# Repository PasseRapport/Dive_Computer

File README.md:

# Freediving Computer

A wrist-mounted freediving computer with tap navigation, wireless charging, and a fully sealed enclosure — no buttons, no external connectors.

---

## V1 — Proof of Concept

Proved two core ideas: **tap-based navigation** via accelerometer and **wireless charging** inside a completely sealed case.

| | |
|---|---|
| **MCU** | ESP32-C3 |
| **Display** | 1.27″ SSD1351 color OLED (128×96) |
| **Pressure** | MS5837-30BA — ±2 mm resolution |
| **Navigation** | LIS2DUX12 tap detection — no buttons |
| **Charging** | LTC4120 wireless receiver — no connectors |
| **Switch** | Magnetic battery cutoff — true 0 µA storage |

### Interface

<p align="center"><em>Tap-based menu navigation — accelerometer detects directional impacts on the casing.</em></p>

### In the Water

<p align="center"><em>Live depth tracking — automatic dive detection and surface recovery timer.</em></p>

### Enclosure

Two-part sandwich assembly sealed by a perimeter O-ring and 12 M2 screws. No dynamic seals anywhere.

---

## V2 — Work in Progress

More compact, better component integration, and additional sensors.

### PCB

### 3D Model

### Exploded View

---

## Android Companion

The offline Android app, Linux BLE watch simulator, and protocol tests live in [`app/`](app/README.md). Development is on a dedicated branch; V1 and V2 firmware remain independent.

## Repository Structure

```
Dive_Computer/
├── V1/         # Prototype — full firmware + hardware source files
├── V2/         # Current revision — in progress
└── app/        # Android companion, BLE simulator and protocol tests
```

See [`V1/README.md`](V1/README.md) for detailed hardware architecture, firmware design, and dive state machine documentation.

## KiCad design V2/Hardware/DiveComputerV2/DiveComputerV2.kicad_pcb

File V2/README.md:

# Freediving Computer V2

## 3D

## Exploded View

## PCB

## Schematic

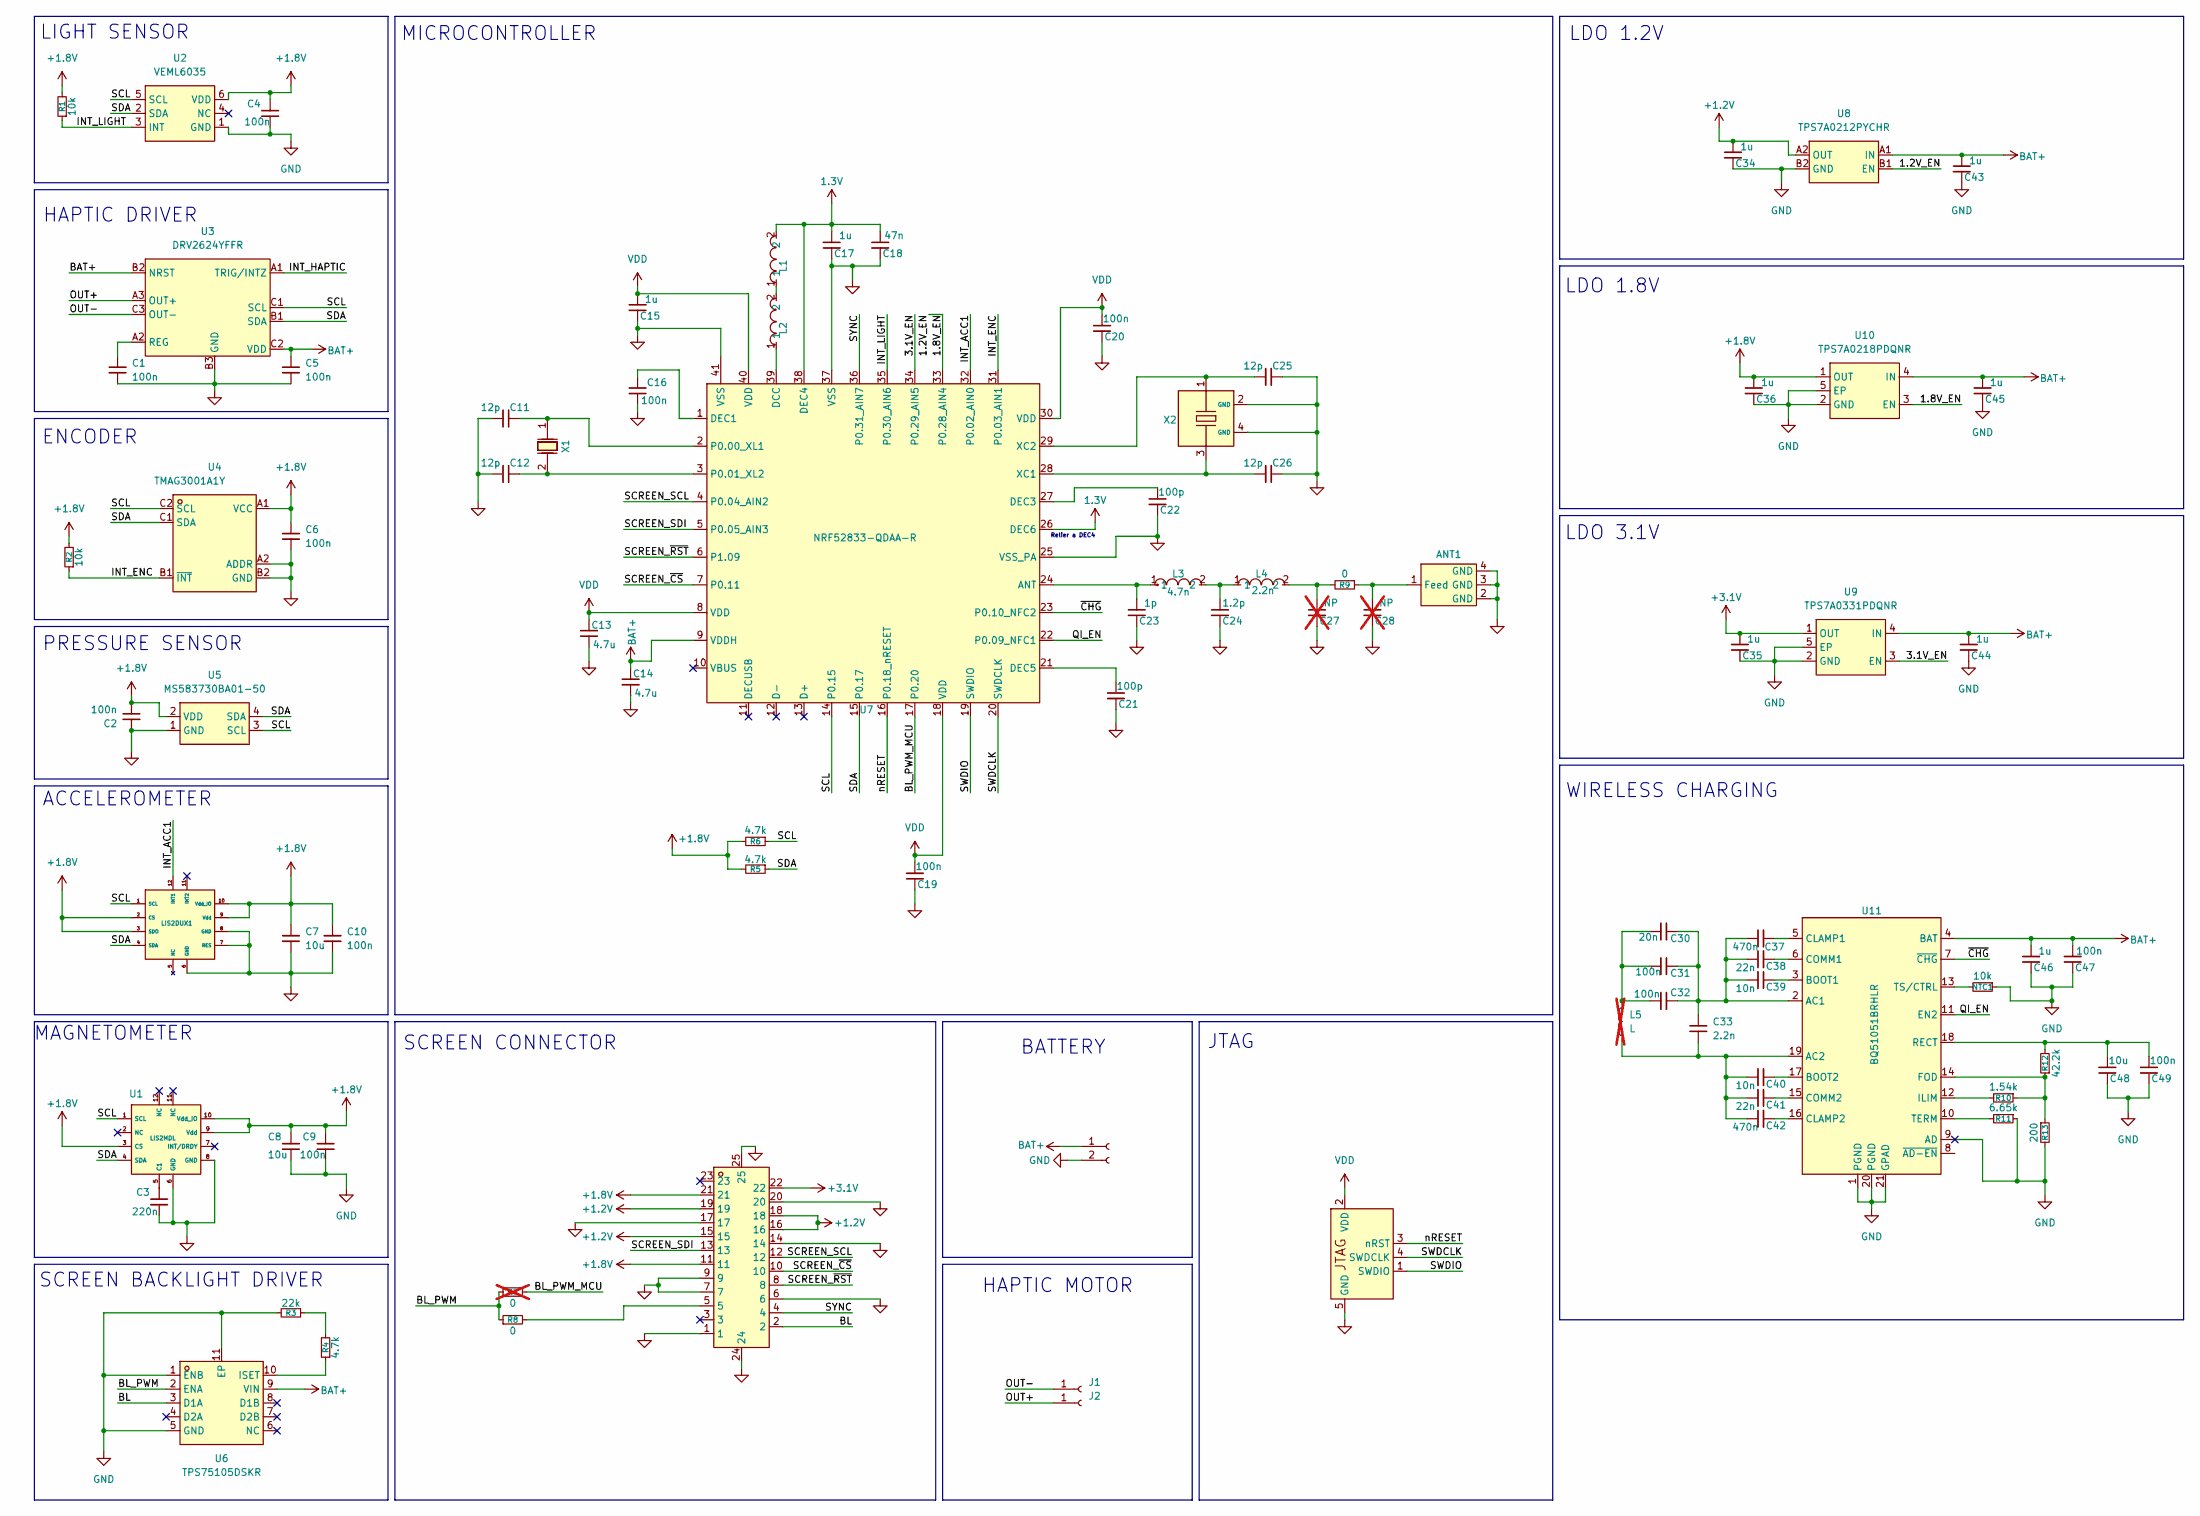
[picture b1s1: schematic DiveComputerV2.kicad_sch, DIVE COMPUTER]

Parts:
ANT1: 2450AT18D0100E; ANT-SMD_4P-L3.2-W1.6; MPN 2450AT18D0100E; LCSC Part C2917718
C1, C2, C4, C5, C6, C9, C10, C47: 100n; C_0402_1005Metric; MPN CL05B104KO5NNNC; LCSC Part C1525
C3: 220n; C_0402_1005Metric; MPN CL05B224KO5NNNC; LCSC Part C16772
C7, C8: 10u; C_0402_1005Metric; LCSC Part C15525
C11, C12, C25, C26: 12p; C_0402_1005Metric; MPN 0402CG120J500NT; LCSC Part C1547
C13, C14: 4.7u; C_0402_1005Metric; LCSC Part C23733
C15, C34, C35, C36, C43, C44, C45, C46: 1u; C_0402_1005Metric; MPN CL05A105KA5NQNC; LCSC Part C52923
C16, C19, C20, C49: 100n; C_0402_1005Metric; MPN CL05B104KB54PNC; LCSC Part C307331
C17: 1u; C_0402_1005Metric; MPN TCC0402X7R105K250AT; LCSC Part C53426846
C18: 47n; C_0402_1005Metric; MPN CL05B473KO5NNNC; LCSC Part C307434
C21, C22: 100p; C_0402_1005Metric; MPN 0402CG101J500NT; LCSC Part C1546
C23: 1p; C_0402_1005Metric; MPN GJM1555C1H1R0WB01D; LCSC Part C72134
C24: 1.2p; C_0402_1005Metric; MPN GJM1555C1H1R2WB01D; LCSC Part C76899
C27, C28: NP; C_0402_1005Metric; not fitted
C29: SAH_Connect
C30: 20n; C_0805_2012Metric; Voltage 50V; Tolerance 1%; MPN GCM21B5C1H203FA16L; LCSC Part C17588990
C31, C32: 100n; C_1206_3216Metric; Voltage 50V; Tolerance 5%; MPN GRM31C5C1H104JA01L; LCSC Part C97946
C33: 2.2n; C_0402_1005Metric; MPN GRM1555C1H222GA01D; LCSC Part C2987940
C37, C42: 470n; C_0402_1005Metric; MPN GRM155R61E474KE01D; LCSC Part C437526
C38, C41: 22n; C_0402_1005Metric; MPN 0402B223K500NT; LCSC Part C1532
C39, C40: 10n; C_0402_1005Metric; MPN GRM155R71H103KA88J; LCSC Part C2840480
C48: 10u; C_0603_1608Metric; MPN CL10A106MA8NRNC; LCSC Part C96446
FPC1: FH35C-23S-0.3SHW; FPC-SMD_23P-P0.60_HRS_FH35C-23S-0.3SHW; MPN FH35C-23S-0.3SHW(50); LCSC Part C2889270
J1, J2: Conn_01x01_Socket; 2292838-3
J3: Conn_01x02_Socket; THT Solder PAD 2pin
L1: LQW15AN15NG00D; IND-SMD_L1.0-W0.5-2; MPN LQW15AN15NG00D; LCSC Part C98055
L2: LQM18DN100M70L; L0603; MPN LQM18DN100M70L; LCSC Part C713281
L3: 4.7n; L0402-RD; MPN LQG15HS4N7B02D; LCSC Part C162543
L4: 2.2n; L0402; MPN LQG15HS2N2B02D; LCSC Part C162540
L5: L; THT Solder PAD 2pin; not fitted
LIS2DUX1: LGA-12_2x2mm_P0.5mm; LCSC Part C17548754
NTC1: 10k; R_0402_1005Metric; MPN NCP15XH103F03RC; LCSC Part C77131
R1, R2: 10k; R_0402_1005Metric; MPN 0402WGF1002TCE; LCSC Part C25744
R3: 22k; R_0402_1005Metric; MPN 0402WGF2202TCE; LCSC Part C25768
R4, R5, R6: 4.7k; R_0402_1005Metric; MPN 0402WGF4701TCE; LCSC Part C25900
R7: 0; R_0402_1005Metric; LCSC Part C17168; not fitted
R8, R9: 0; R_0402_1005Metric; LCSC Part C17168
R10: 1.54k; R_0402_1005Metric; MPN CRCW04021K54FKED; LCSC Part C2085404
R11: 6.65k; R_0402_1005Metric; MPN CRCW04026K65FKED; LCSC Part C2076542
R12: 42.2k; R_0402_1005Metric; MPN FRC0402F4222TS; LCSC Part C5126131
R13: 200; R_0402_1005Metric; MPN 0402WGF2000TCE; LCSC Part C25087
U1: LIS2MDL; VLGA-12_L2.0-W2.0-P0.50-BL; MPN LIS2MDLTR; LCSC Part C919695
U2: VEML6035; SMD-6_L2.0-W2.0-P0.65-BL; MPN VEML6035; LCSC Part C2655158
U3: DRV2624YFFR; DSBGA-9_L1.4-W1.3-R3-C3-P0.40-BL; MPN DRV2624YFFR; LCSC Part C881487
U4: TMAG3001A1Y; BGA-6_L1.3-W0.8-P0.40-TL_PTMAG3001A2YBGR; MPN TMAG3001A1YBGR; LCSC Part C29073186
U5: MS583730BA01-50; SENSOR-SMD_4P-L3.3-W3.3-P2.00-BL; MPN MS583730BA01-50; LCSC Part C2887941
U6: TPS75105DSKR; WSON-10_L2.5-W2.5-W0.50-TL-EP; MPN TPS75105DSKR; LCSC Part C2859928
U7: NRF52833-QDAA-R; QFN-40_L5.0-W5.0-P0.40-TL-EP3.6; MPN nRF52833-QDAA-R; LCSC Part C2895249
U8: TPS7A0212PYCHR; DSBGA-4_L0.7-W0.7-R2-C2-P0.35-BL; MPN TPS7A0212PYCHR; LCSC Part C2918962
U9: TPS7A0331PDQNR; X2SON-4_L1.0-W1.0-P0.65-TL-EP; MPN TPS7A0331PDQNR; LCSC Part C2864441
U10: TPS7A0218PDQNR; X2SON-4_L1.0-W1.0-P0.65-TL-EP; MPN TPS7A0218PDQNR; LCSC Part C2862166
U11: BQ51051BRHLR; VQFN-20_L4.5-W3.5-P0.50-BL-EP_BQ24100RHLR; MPN BQ51051BRHLR; LCSC Part C2876732
X1: CM8V-T1A-32.768KHZ-9PF-20PPM-TB-QC; CRYSTAL-SMD_L2.0-W1.2; MPN CM8V-T1A-32.768kHz-9pF-20PPM-TB-QC; LCSC Part C5280691
X2: ECS-320-CDX-2152; CRYSTAL-SMD_4P-L1.6-W1.2-BL; MPN ECS-320-CDX-2152; LCSC Part C5686354

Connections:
1.3V: C17.2, C18.2, L1.2, U7.26 (DEC6), U7.38 (DEC4)
+1.2V: C34.2, FPC1.15, FPC1.16, FPC1.18, FPC1.19, U8.A2 (OUT)
+1.8V: C2.2, C4.1, C6.2, C7.1, C8.1, C9.1, C10.1, C36.2, FPC1.11, FPC1.21, LIS2DUX1.2 (CS), LIS2DUX1.3 (SDO), LIS2DUX1.9 (Vdd), LIS2DUX1.10 (Vdd_IO), R1.2, R2.2, R5.2, R6.2, U1.3 (CS), U1.9 (Vdd), U1.10 (Vdd_IO), U2.6 (VDD), U4.A1 (VCC), U5.2 (VDD), U10.1 (OUT)
+3.1V: C35.2, FPC1.22, U9.1 (OUT)
/1.2V_EN: U7.33 (P0.28_AIN4), U8.B1 (EN), U10.3 (EN)
/3.1V_EN: U7.34 (P0.29_AIN5), U9.3 (EN)
/BL: FPC1.2, U6.3 (D1A)
/BL_PWM: R7.1, R8.1, U6.2 (ENA)
/BL_PWM_MCU: R7.2, U7.17 (P0.20)
/INT_ACC1: LIS2DUX1.12 (INT1), U7.32 (P0.02_AIN0)
/INT_ENC: R2.1, U4.B1 (~INT), U7.31 (P0.03_AIN1)
/INT_HAPTIC: U3.A1 (TRIG/INTZ)
/INT_LIGHT: R1.1, U2.3 (INT), U7.35 (P0.30_AIN6)
/OUT+: J2.1 (Pin_1_1), U3.A3 (OUT+)
/OUT-: J1.1 (Pin_1_1), U3.C3 (OUT-)
/QI_EN: U7.22 (P0.09_NFC1), U11.11 (EN2)
/SCL: LIS2DUX1.1 (SCL), R6.1, U1.1 (SCL), U2.5 (SCL), U3.C1 (SCL), U4.C2 (SCL), U5.3 (SCL), U7.14 (P0.15)
/SCREEN_SCL: FPC1.12, U7.4 (P0.04_AIN2)
/SCREEN_SDI: FPC1.13, U7.5 (P0.05_AIN3)
/SCREEN_~CS: FPC1.10, U7.7 (P0.11)
/SCREEN_~RST: FPC1.8, U7.6 (P1.09)
/SDA: LIS2DUX1.4 (SDA), R5.1, U1.4 (SDA), U2.2 (SDA), U3.B1 (SDA), U4.C1 (SDA), U5.4 (SDA), U7.15 (P0.17)
/SWDCLK: C29.4 (SWDCLK), U7.20 (SWDCLK)
/SWDIO: C29.1 (SWDIO), U7.19 (SWDIO)
/SYNC: FPC1.4, U7.36 (P0.31_AIN7)
/nRESET: C29.3 (nRST), U7.16 (P0.18_nRESET)
/~CHG: U7.23 (P0.10_NFC2), U11.7 (~CHG)
BAT+: C5.1, C14.1, C43.2, C44.2, C45.2, C46.2, C47.2, J3.1, U3.B2 (NRST), U3.C2 (VDD), U6.9 (VIN), U7.9 (VDDH), U8.A1 (IN), U9.4 (IN), U10.4 (IN), U11.4 (BAT)
GND: ANT1.2 (GND), ANT1.3 (GND), ANT1.4 (GND), C1.2, C2.1, C3.2, C4.2, C5.2, C6.1, C7.2, C8.2, C9.2, C10.2, C11.2, C12.2, C13.2, C14.2, C15.1, C16.2, C17.1, C18.1, C19.1, C20.1, C21.1, C22.1, C23.1, C24.1, C25.1, C26.1, C27.1, C28.1, C29.5 (GND), C34.1, C35.1, C36.1, C43.1, C44.1, C45.1, C46.1, C47.1, C48.1, C49.1, FPC1.1, FPC1.6, FPC1.7, FPC1.9, FPC1.14, FPC1.17, FPC1.20, FPC1.24, FPC1.25, J3.2, LIS2DUX1.6 (GND), LIS2DUX1.7 (RES), LIS2DUX1.8 (GND), NTC1.1, R3.2, R11.1, R13.2, U1.6 (GND), U1.8 (GND), U2.1 (GND), U3.B3 (GND), U4.A2 (ADDR), U4.B2 (GND), U5.1 (GND), U6.1 (ENB), U6.5 (GND), U6.11 (EP), U7.25 (VSS_PA), U7.37 (VSS), U7.41 (VSS), U8.B2 (GND), U9.2 (GND), U9.5 (EP), U10.2 (GND), U10.5 (EP), U11.1 (PGND), U11.9 (AD), U11.20 (PGND), U11.21 (GPAD), X2.2 (GND), X2.4 (GND)
unnamed: ANT1.1 (Feed), C28.2, R9.1
unnamed: C24.2, L3.2, L4.1
unnamed: C27.2, L4.2, R9.2
unnamed: C30.1, C31.1, C32.1, L5.2
unnamed: FPC1.5, R8.2
unnamed: L1.1, L2.2
unnamed: R3.1, R4.2
unnamed: C3.1, U1.5 (C1)
unnamed: C1.1, U3.A2 (REG)
unnamed: R4.1, U6.10 (ISET)
unnamed: C23.2, L3.1, U7.24 (ANT)
unnamed: L2.1, U7.39 (DCC)
unnamed: C16.1, U7.1 (DEC1)
unnamed: C22.2, U7.27 (DEC3)
unnamed: C21.2, U7.21 (DEC5)
unnamed: C11.1, U7.2 (P0.00_XL1), X1.1
unnamed: C12.1, U7.3 (P0.01_XL2), X1.2
unnamed: C26.2, U7.28 (XC1), X2.3
unnamed: C25.2, U7.29 (XC2), X2.1
unnamed: C30.2, C31.2, C32.2, C33.1, C37.1, C38.1, C39.1, U11.2 (AC1)
unnamed: C33.2, C40.1, C41.1, C42.1, L5.1, U11.19 (AC2)
unnamed: C39.2, U11.3 (BOOT1)
unnamed: C40.2, U11.17 (BOOT2)
unnamed: C37.2, U11.5 (CLAMP1)
unnamed: C42.2, U11.16 (CLAMP2)
unnamed: C38.2, U11.6 (COMM1)
unnamed: C41.2, U11.15 (COMM2)
unnamed: R10.1, R12.1, R13.1, U11.14 (FOD)
unnamed: R10.2, U11.12 (ILIM)
unnamed: C48.2, C49.2, R12.2, U11.18 (RECT)
unnamed: R11.2, U11.10 (TERM)
unnamed: NTC1.2, U11.13 (TS/CTRL)
VDD: C13.1, C15.2, C19.2, C20.2, C29.2 (VDD), U7.8 (VDD), U7.18 (VDD), U7.30 (VDD), U7.40 (VDD)

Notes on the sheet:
PRESSURE SENSOR
MICROCONTROLLER
SCREEN BACKLIGHT DRIVER
BATTERY
SCREEN CONNECTOR
ACCELEROMETER
HAPTIC MOTOR
JTAG
ENCODER
LDO 1.8V
WIRELESS CHARGING
HAPTIC DRIVER
LDO 3.1V
LDO 1.2V
MAGNETOMETER
Relier a DEC4
LIGHT SENSOR

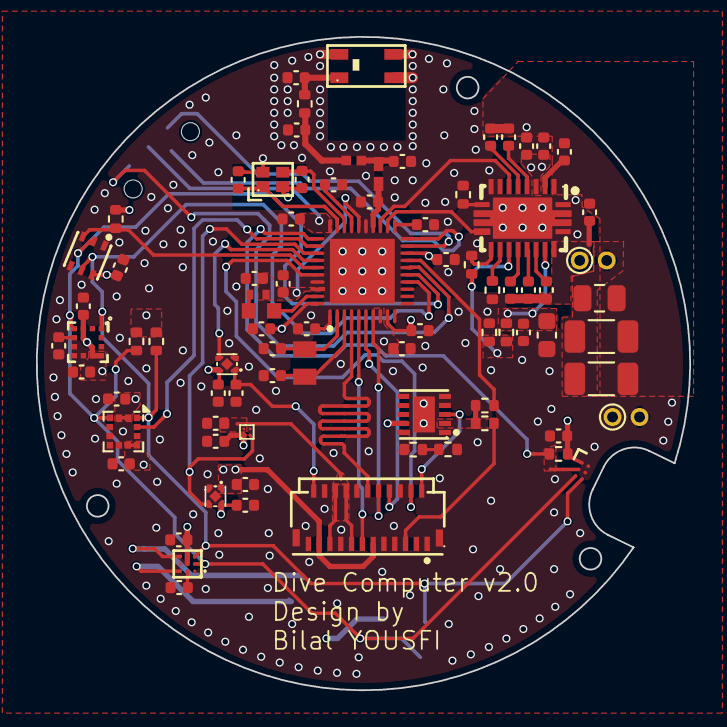
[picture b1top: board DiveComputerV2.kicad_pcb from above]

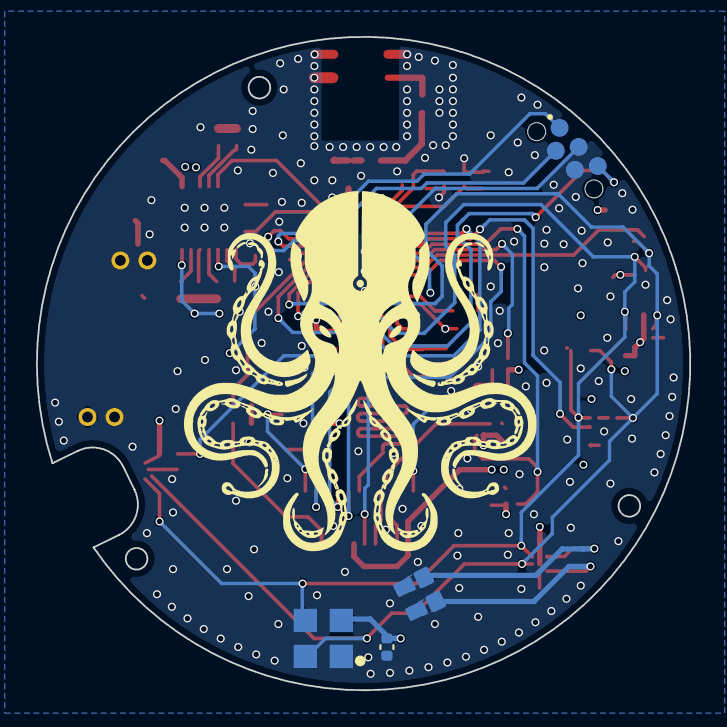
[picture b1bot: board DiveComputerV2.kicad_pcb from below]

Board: 4 copper layers, 36.3 x 36.3 mm, 87 parts (5 on the bottom side), 61 nets.

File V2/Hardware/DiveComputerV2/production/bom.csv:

Designator,Footprint,Quantity,Value,LCSC Part #
ANT1,ANT-SMD_4P-L3.2-W1.6,1,2450AT18D0100E,C2917718
"C1, C10, C2, C4, C47, C5, C6, C9",0402,8,100n,C1525
"C11, C12, C25, C26",0402,4,12p,C1547 
"C13, C14",0402,2,4.7u,C23733
"C15, C34, C35, C36, C43, C44, C45, C46",0402,8,1u,C52923
"C16, C19, C20, C49",0402,4,100n,C307331
C17,0402,1,1u,C53426846
C18,0402,1,47n,C307434
"C21, C22",0402,2,100p,C1546
C23,0402,1,1p,C72134
C24,0402,1,1.2p,C76899
C29,SAH_Connect,1,~,
C3,0402,1,220n,C16772
C30,0805,1,20n,C17588990
"C31, C32",1206,2,100n,C97946
C33,0402,1,2.2n,C2987940
"C37, C42",0402,2,470n,C437526
"C38, C41",0402,2,22n,C1532
"C39, C40",0402,2,10n,C2840480
C48,0603,1,10u,C96446
"C7, C8",0402,2,10u,C15525
FPC1,FPC-SMD_23P-P0.60_HRS_FH35C-23S-0.3SHW,1,FH35C-23S-0.3SHW,C2889270
"J1, J2",2292838-3,2,Conn_01x01_Socket,
L1,IND-SMD_L1.0-W0.5-2,1,LQW15AN15NG00D,C98055
L2,L0603,1,LQM18DN100M70L,C713281
L3,L0402-RD,1,4.7n,C162543
L4,L0402,1,2.2n,C162540
LIS2DUX1,LGA-12_2x2mm_P0.5mm,1,~,C17548754
NTC1,0402,1,10k,C77131
"R1, R2",0402,2,10k,C25744
R10,0402,1,1.54k,C2085404
R11,0402,1,6.65k,C2076542
R12,0402,1,42.2k,C5126131
R13,0402,1,200,C25087
R3,0402,1,22k,C25768
"R4, R5, R6",0402,3,4.7k,C25900
"R8, R9",0402,2,0,C17168 
U1,VLGA-12_L2.0-W2.0-P0.50-BL,1,LIS2MDL,C919695
U10,X2SON-4_L1.0-W1.0-P0.65-TL-EP,1,TPS7A0218PDQNR,C2862166
U11,VQFN-20_L4.5-W3.5-P0.50-BL-EP_BQ24100RHLR,1,BQ51051BRHLR,C2876732
U2,SMD-6_L2.0-W2.0-P0.65-BL,1,VEML6035,C2655158
U3,DSBGA-9_L1.4-W1.3-R3-C3-P0.40-BL,1,DRV2624YFFR,C881487
U4,BGA-6_L1.3-W0.8-P0.40-TL_PTMAG3001A2YBGR,1,TMAG3001A1Y,C29073186
U5,SENSOR-SMD_4P-L3.3-W3.3-P2.00-BL,1,MS583730BA01-50,C2887941
U6,WSON-10_L2.5-W2.5-W0.50-TL-EP,1,TPS75105DSKR,C2859928
U7,QFN-40_L5.0-W5.0-P0.40-TL-EP3.6,1,NRF52833-QDAA-R,C2895249
U8,DSBGA-4_L0.7-W0.7-R2-C2-P0.35-BL,1,TPS7A0212PYCHR,C2918962
U9,X2SON-4_L1.0-W1.0-P0.65-TL-EP,1,TPS7A0331PDQNR,C2864441
X1,CRYSTAL-SMD_L2.0-W1.2,1,CM8V-T1A-32.768KHZ-9PF-20PPM-TB-QC,C5280691
X2,CRYSTAL-SMD_4P-L1.6-W1.2-BL,1,ECS-320-CDX-2152,C5686354

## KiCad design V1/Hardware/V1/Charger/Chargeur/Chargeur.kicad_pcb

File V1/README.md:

# Freediving Computer

A freediving computer prototype I built to test two main ideas: **tap navigation via accelerometer** and **wireless charging** in a completely sealed case.

As a maker, building waterproof buttons and moving parts that survive water pressure without leaking is nearly impossible. To avoid leaks, I skipped physical buttons and external connectors entirely:
1. **Tap navigation** — tapping the case scrolls and selects menus; the accelerometer detects the shock direction.
2. **Wireless charging** — sealed inside the case with an LTC4120 receiver, powered by a custom induction dock.
3. **Magnetic power switch** — an external magnet disconnects the battery so it doesn't drain when stored.
4. **Custom 4-layer PCB** — designed around the form factor of an off-the-shelf color OLED module.

> **Status**: This V1 worked and proved the concept. I am now working on a **V2** that is more compact, with better integration and additional features.

---

## Demo

<p align="center"><em>Tap-based navigation through the interface — accelerometer detects directional impacts on the casing.</em></p>

<p align="center"><em>Live depth tracking during a test — automatic dive detection and surface recovery timer.</em></p>

---

## Key Features

| Category | Details |
|---|---|
| **Depth & Temperature** | Real-time tracking via MS5837-30BA (±2 mm resolution, 300–1200 hPa). Automatic fresh/salt water density compensation. |
| **Dive State Machine** | Auto-triggers at 1.0 m depth. Tracks dive time, max depth per dive, and session statistics. |
| **Surface Recovery Timer** | Starts automatically on surfacing. Color-coded: red until 2× dive time, then green. Auto-hides after 10 min. |
| **Session Statistics** | Max dive time, max depth, total dives, and device run time — all tracked per session. |
| **Tap Navigation** | LIS2DUX12 accelerometer detects directional taps on the casing. Left/right to scroll, down to select. No buttons, no dynamic seals. |
| **Magnetic Battery Cutoff** | Integrated magnetic switch isolates the LiPo battery with an external magnet (true 0 µA shelf storage while sealed). |
| **Wireless Charging** | Completely sealed enclosure — power delivered through the case via LTC4120 wireless power receiver. |
| **Display** | 1.27" SSD1351 color OLED (128×96), driven over SPI with DMA. LVGL handles 60 fps animated transitions. |
| **Battery Monitoring** | ADC with hardware calibration curve. Voltage divider maps LiPo range (3.0–4.2 V) to percentage. |
| **Deep Sleep** | Full power-off via menu. GPIO wakeup from accelerometer interrupt. OLED and SPI bus shut down cleanly. |

---

## Mechanical Design

The housing is a two-part sandwich assembly designed without push-buttons, external connectors, or dynamic seals. Waterproofing relies entirely on static seals: a perimeter O-ring evenly compressed between the two halves by 12 M2 screws, and a front protective glass bonded with UV-cure resin. The only physical control is an external magnetic slider that switches power through the solid case wall without any hull penetration.

<p align="center">
  <a href="https://cad.onshape.com/documents/cc2f090fad22f578b68190d0/w/ffbf50c58a8e366da5acdcdc/e/88baec5796e801b1a2b4a1f3">
    View the 3D model on Onshape ↗
  </a>
</p>

---

## Hardware Architecture

The electronics are split between the wrist unit and a dedicated charging dock.

### 1. Dive Computer Board (Wrist Unit)

The core electronics are built around a custom **4-layer PCB** designed in KiCad, dimensioned to mate directly with an off-the-shelf color OLED module:

- **Form Factor & Display**: Sourced a compact 1.27" 128×96 color OLED module (SSD1351 controller, SPI) and tailored the custom 4-layer PCB and enclosure footprint around this geometry.
- **MCU**: ESP32-C3 (RISC-V core, low power modes, BLE).
- **Pressure Sensor**: TE MS5837-30BA (gel-protected submersible pressure & temperature sensor on I2C).
- **Accelerometer**: ST LIS2DUX12 (ultra-low-power, configured for shock/tap detection with hardware interrupt).
- **Wireless Power Receiver**: Analog Devices LTC4120 with an internal Würth planar receiver coil (WE-WPCC-RX), delivering CC/CV charging to the internal 3.7V LiPo cell.
- **Magnetic Power Switch**: Integrated Hall-effect sensor / magnetic switch controlling a P-MOSFET gate, enabling complete physical battery disconnection via an external magnet without unsealing the housing.

| Component | Part | Role |
|---|---|---|
| MCU | ESP32-C3 | RISC-V core, sensor aggregation, LVGL rendering |
| Pressure Sensor | MS5837-30BA | Absolute pressure & temperature (I2C @ 100 kHz) |
| Accelerometer | LIS2DUX12 | Tap detection with hardware interrupt (I2C) |
| Wireless Charger RX | LTC4120 | Wireless power receiver & CC/CV LiPo charger |
| Magnetic Disconnect | A1102 + P-MOS | Physical battery isolation via external magnet (0 µA storage) |
| Display Module | SSD1351 (Off-the-shelf) | 1.27" 128×96 color OLED (SPI with DMA) |
| Battery | LiPo 3.7V | Single cell, monitored via calibrated ADC voltage divider |

### 2. Wireless Charger Dock (Transmitter)

A companion transmitter base powered via USB-C:

| Component | Part | Role |
|---|---|---|
| Transmitter IC | LTC4125 | 5W AutoResonant wireless power transmitter |
| Transmit Coil | Würth WE-WPCC-TX | 24 µH primary coil for inductive power transfer |
| Input | USB-C (5V) | Power supply |

Source files (KiCad projects, gerbers, BOM): [`Hardware/V1/`](Hardware/V1/)

---

## Software Architecture

The firmware is written in **C** on **ESP-IDF** with **FreeRTOS**. The codebase follows an MVC pattern:

```
Software/DiveComputer/main/
├── main.c                  # App entry, event loop, screen state machine
├── components/
│   ├── pressure_sensor.c   # MS5837 driver, depth calculation, calibration
│   ├── accelerometer.c     # LIS2DUX12 tap detection (ISR + burst analysis)
│   ├── battery.c           # ADC with hardware calibration curve
│   └── oled_display.c      # SSD1351 init, SPI+DMA, LVGL driver
└── ui/
    ├── ui_model.h          # Global state structure (dive_state_t)
    ├── ui_controller.c     # Dive logic, timers, brightness control
    ├── ui_layout.c         # All LVGL screens and refresh functions
    └── ui_layout.h         # Public UI API
```

### Task Model

| Task | Core | Priority | Rate | Role |
|---|---|---|---|---|
| `dive_sensor_task` | 1 | 5 | 4 Hz | Reads pressure sensor, computes depth, updates model |
| `lvgl_port_task` | 0 | 5 | 100 Hz | LVGL rendering and screen refresh |
| `tap_analyzer_task` | 0 | 10 | Event-driven | Wakes on accelerometer interrupt, analyzes shock direction |
| Main loop | 0 | 1 | 50 Hz | Polls tap events, drives screen state machine |

### Dive State Machine

```
                 depth > 1.0m
   ┌──────────┐ ───────────────> ┌──────────┐
   │ SURFACE  │                  │  DIVING  │ <──────┐
   └──────────┘                  └──────────┘        │
        ^                             │              │ depth > 1.0m
        │                             │ depth < 0.3m │ (next dive)
        │                             v              │
        │                      ┌─────────────┐       │
        └───────────────────── │  POST-DIVE  │ ──────┘
           recovery >= 10 min  │ (Recovery)  │
                               └─────────────┘

```

### Tap Detection Pipeline

The accelerometer's hardware tap interrupt wakes the ESP32, which performs a 100-sample burst read (~10 ms) to capture the full shock waveform. The axis with the largest amplitude delta wins, and its sign determines the direction. A 2000-unit noise floor filter rejects accidental vibrations.

```
[HW Interrupt] ──> [ISR Queue] ──> [Burst Read (100 samples)] ──> [Axis Analysis] ──> [Direction Filter] ──> [UI Event]
```

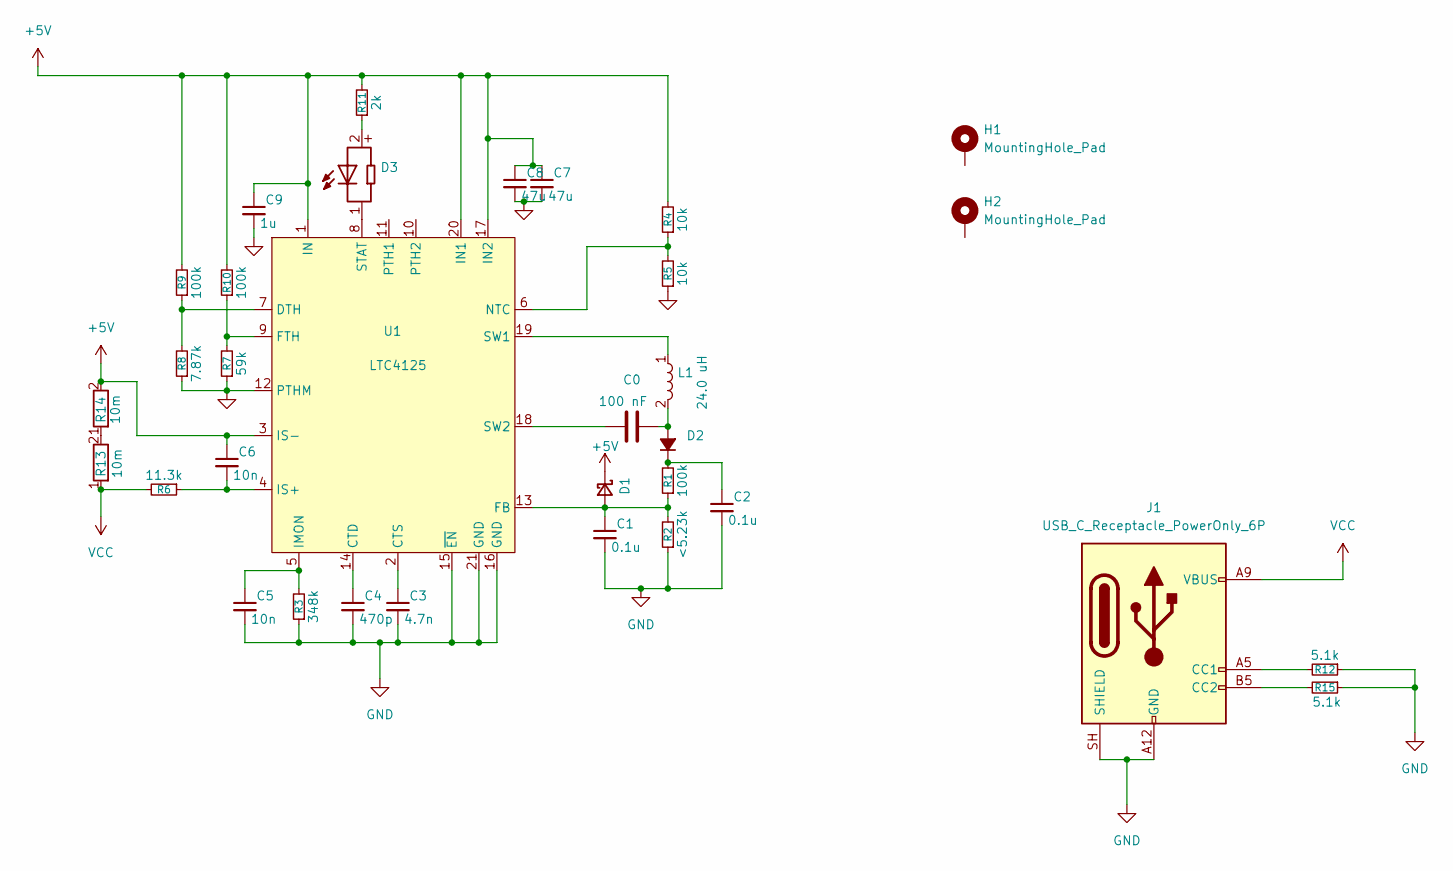
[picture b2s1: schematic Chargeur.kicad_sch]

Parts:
C0: 100 nF; C_Wurth_WCAP-FTBP-P7.5L10.5W5H11; Voltage 160; Part Number 890443322001CS
C1, C2: 0.1u; C_0603_1608Metric
C3: 4.7n; C_0603_1608Metric
C4: 470p; C_0603_1608Metric
C5, C6: 10n; C_0603_1608Metric
C7, C8: 47u; C_1206_3216Metric
C9: 1u; C_1206_3216Metric
D1: D_Schottky_Small; D_MicroSMP_LargeCathode
D2: D_Small_Filled; D_SOD-523
D3: 3535_150353BS74500; D_Wurth_WL-SMDC-3535; Part Number 150353BS74500
H1, H2: MountingHole_Pad; MountingHole_3.2mm_M3_DIN965_Pad
J1: USB_C_Receptacle_PowerOnly_6P; USB_C_Receptacle_GCT_USB4125-xx-x-0190_6P_TopMnt_Horizontal
L1: 24.0 uH; L_Wurth_WE-WPCC-TX_760308101107; Part Number 760308101107
R1, R9, R10: 100k; R_0603_1608Metric
R2: <5.23k; R_0603_1608Metric
R3: 348k; R_0603_1608Metric
R4, R5: 10k; R_0603_1608Metric
R6: 11.3k; R_0603_1608Metric
R7: 59k; R_0603_1608Metric
R8: 7.87k; R_0603_1608Metric
R11: 2k; R_0603_1608Metric
R12, R15: 5.1k; R_0603_1608Metric
R13, R14: 10 mohm; R_Wurth_WRIS-PSMB-1206_L3.2W1.6H0.28; Part Number 580060732021
U1: LTC4125; QFN-20-1EP_4x5mm_P0.5mm_EP2.65x3.65mm

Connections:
+5V: C6.1, C7.1, C8.1, C9.1, D1.1 (K), R4.2, R9.2, R10.2, R11.2, R14.2, U1.1 (IN), U1.3 (IS-), U1.17 (IN2), U1.20 (IN1)
GND: C1.2, C2.2, C3.2, C4.2, C5.2, C7.2, C8.2, C9.2, J1.A12 (GND), J1.B12 (GND), J1.SH (SHIELD), R2.1, R3.1, R5.1, R7.1, R8.1, R12.1, R15.1, U1.12 (PTHM), U1.15 (~EN), U1.16 (GND), U1.21 (GND)
unnamed: C1.1, D1.2 (A), R1.1, R2.2, U1.13 (FB)
unnamed: C0.2, D2.2 (A), L1.2
unnamed: C2.1, D2.1 (K), R1.2
unnamed: D3.2 (+), R11.1
unnamed: D3.1 (-), U1.8 (STAT)
unnamed: J1.A5 (CC1), R12.2
unnamed: J1.B5 (CC2), R15.2
unnamed: R13.2, R14.1
unnamed: C4.1, U1.14 (CTD)
unnamed: C3.1, U1.2 (CTS)
unnamed: R8.2, R9.1, U1.7 (DTH)
unnamed: R7.2, R10.1, U1.9 (FTH)
unnamed: C5.1, R3.2, U1.5 (IMON)
unnamed: C6.2, R6.1, U1.4 (IS+)
unnamed: R4.1, R5.2, U1.6 (NTC)
unnamed: L1.1, U1.19 (SW1)
unnamed: C0.1, U1.18 (SW2)
VCC: J1.A9 (VBUS), J1.B9 (VBUS), R6.2, R13.1

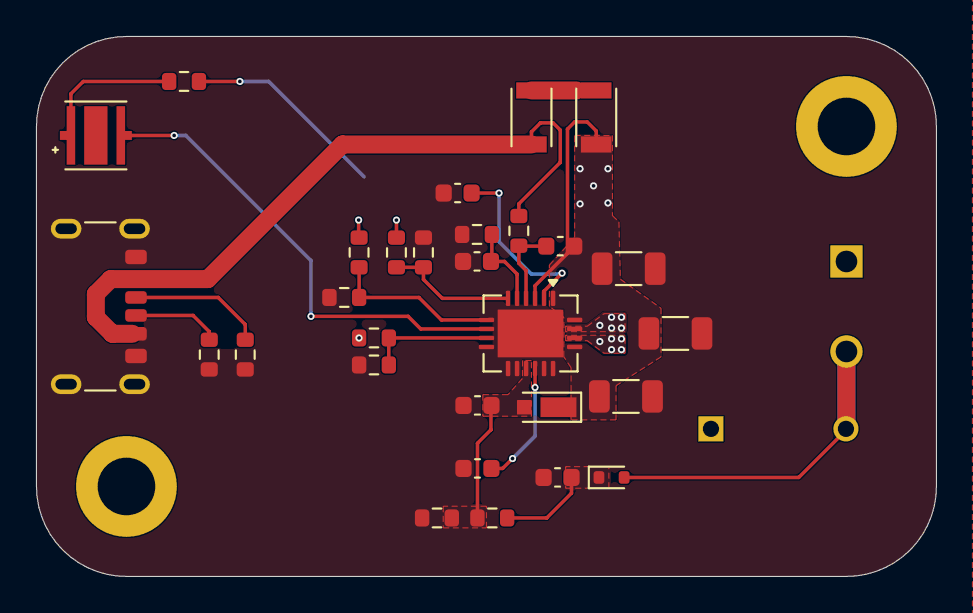
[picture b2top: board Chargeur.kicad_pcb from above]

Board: 2 copper layers, 50.0 x 30.0 mm, 33 parts (0 on the bottom side), 20 nets.

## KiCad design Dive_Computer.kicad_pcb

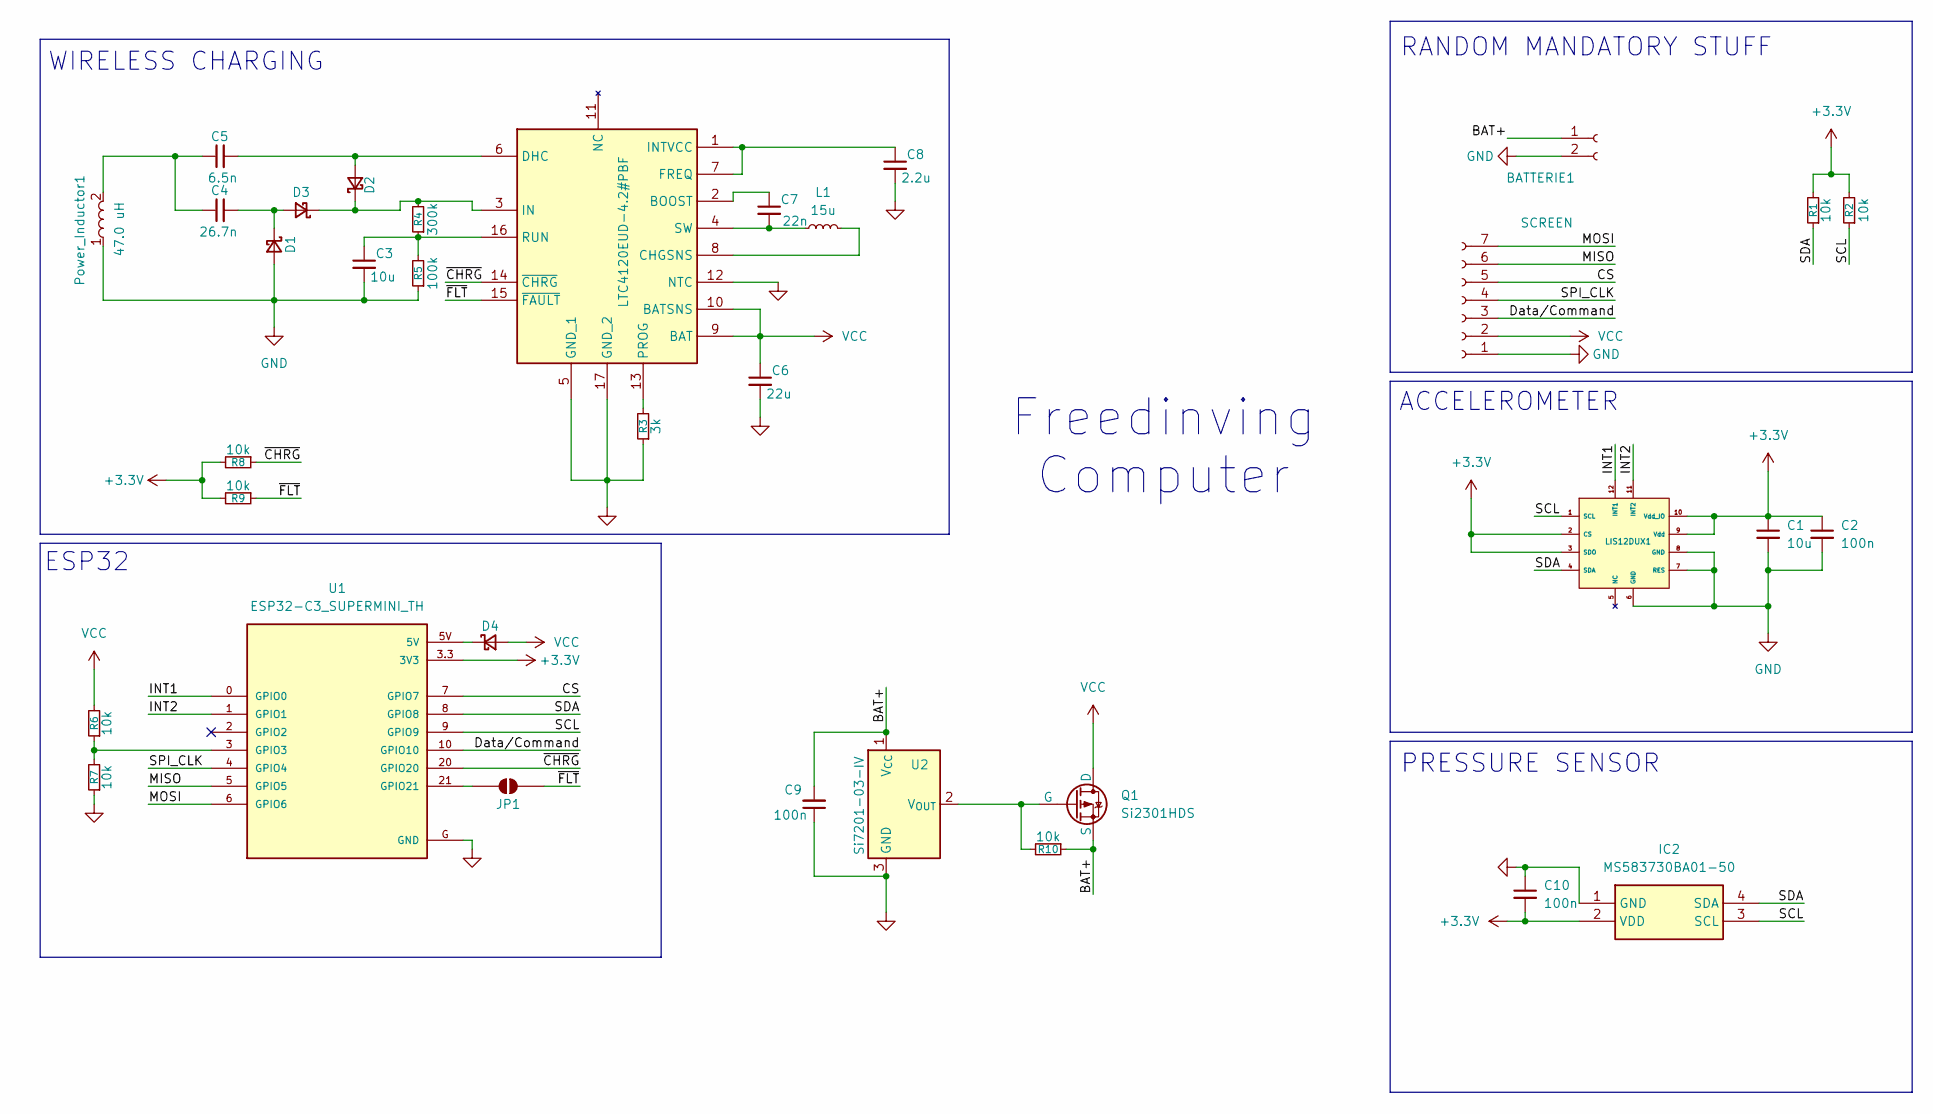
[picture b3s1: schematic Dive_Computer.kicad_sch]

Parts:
BATTERIE1: BAT; Hirose_DF13-02P-1.25DSA_1x02_P1.25mm_Vertical
C1: 10u; C_0603_1608Metric
C2, C9, C10: 100n; C_0603_1608Metric
C3: 10u; C_1210_3225Metric
C4: 26.7n; C_0603_1608Metric
C5: 6.5n; C_0603_1608Metric
C6: 22u; C_0603_1608Metric
C7: 22n; C_0603_1608Metric
C8: 2.2u; C_0603_1608Metric
D1, D2, D3, D4: MSS2P2-M3/89A; D_MicroSMP_LargeCathode
IC1: LTC4120EUD-4.2#PBF; QFN-16-1EP_3x3mm_P0.5mm_EP1.7x1.7mm; Manufacturer_Part_Number LTC4120EUD-4.2#PBF; Mouser Part Number 584-C4120EUD-4.2PBF
IC2: MS583730BA01-50; TE_MS5837-xxBA; Manufacturer_Part_Number MS583730BA01-50; Mouser Part Number 824-MS583730BA01-50
J1: SCREEN; Hirose_DF13-07P-1.25DSA_1x07_P1.25mm_Vertical
JP1: SolderJumper_2_Open; SolderJumper-2_P1.3mm_Open_RoundedPad1.0x1.5mm
L1: 15u; L_APV_ANR4018
LIS12DUX1: LGA-12_2x2mm_P0.5mm
Power_Inductor1: 47.0 uH; PinHeader_1x02_P2.54mm_Vertical; Part Number 760308101303
Q1: Si2301HDS; TSOT-23
R1, R2, R6, R7, R8, R9, R10: 10k; R_0603_1608Metric
R3: 3k; R_0603_1608Metric
R4: 300k; R_0603_1608Metric
R5: 100k; R_0603_1608Metric
U1: ESP32-C3_SUPERMINI_TH; MODULE_ESP32-C3_SUPERMINI_TH
U2: Si7201-03-IV; SOT-23

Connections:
+3.3V: C1.1, C2.1, C10.2, IC2.2 (VDD), LIS12DUX1.2 (CS), LIS12DUX1.3 (SDO), LIS12DUX1.9 (Vdd), LIS12DUX1.10 (Vdd_IO), R1.2, R2.2, R8.2, R9.2, U1.3.3 (3V3)
/BAT+: BATTERIE1.1, C9.2, Q1.3 (S), R10.1, U2.1 (V_{CC})
/CS: J1.5, U1.7 (GPIO7)
/Data/Command: J1.3, U1.10 (GPIO10)
/INT1: LIS12DUX1.12 (INT1), U1.0 (GPIO0)
/INT2: LIS12DUX1.11 (INT2), U1.1 (GPIO1)
/MISO: J1.6, U1.5 (GPIO5)
/MOSI: J1.7, U1.6 (GPIO6)
/SCL: IC2.3 (SCL), LIS12DUX1.1 (SCL), R2.1, U1.9 (GPIO9)
/SDA: IC2.4 (SDA), LIS12DUX1.4 (SDA), R1.1, U1.8 (GPIO8)
/SPI_CLK: J1.4, U1.4 (GPIO4)
/~CHRG: IC1.14 (~CHRG), R8.1, U1.20 (GPIO20)
/~FLT: IC1.15 (~FAULT), JP1.2 (B), R9.1
GND: BATTERIE1.2, C1.2, C2.2, C3.2, C6.2, C8.2, C9.1, C10.1, D1.2 (A), IC1.5 (GND_1), IC1.12 (NTC), IC1.17 (GND_2), IC2.1 (GND), J1.1, LIS12DUX1.6 (GND), LIS12DUX1.7 (RES), LIS12DUX1.8 (GND), Power_Inductor1.1, R3.1, R5.1, R7.1, U1.G (GND), U2.3 (GND)
unnamed: C4.1, C5.1, Power_Inductor1.2
unnamed: C4.2, D1.1 (K), D3.2 (A)
unnamed: C5.2, D2.2 (A), IC1.6 (DHC)
unnamed: D2.1 (K), D3.1 (K), IC1.3 (IN), R4.2
unnamed: D4.1 (K), U1.5V
unnamed: C7.1, IC1.2 (BOOST)
unnamed: IC1.8 (CHGSNS), L1.2
unnamed: C8.1, IC1.1 (INTVCC), IC1.7 (FREQ)
unnamed: IC1.13 (PROG), R3.2
unnamed: C3.1, IC1.16 (RUN), R4.1, R5.2
unnamed: C7.2, IC1.4 (SW), L1.1
unnamed: JP1.1 (A), U1.21 (GPIO21)
unnamed: Q1.2 (G), R10.2, U2.2 (V_{OUT})
unnamed: R6.1, R7.2, U1.3 (GPIO3)
VCC: C6.1, D4.2 (A), IC1.9 (BAT), IC1.10 (BATSNS), J1.2, Q1.1 (D), R6.2

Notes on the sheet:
PRESSURE SENSOR
ACCELEROMETER
RANDOM MANDATORY STUFF
Freedinving Computer
ESP32
WIRELESS CHARGING

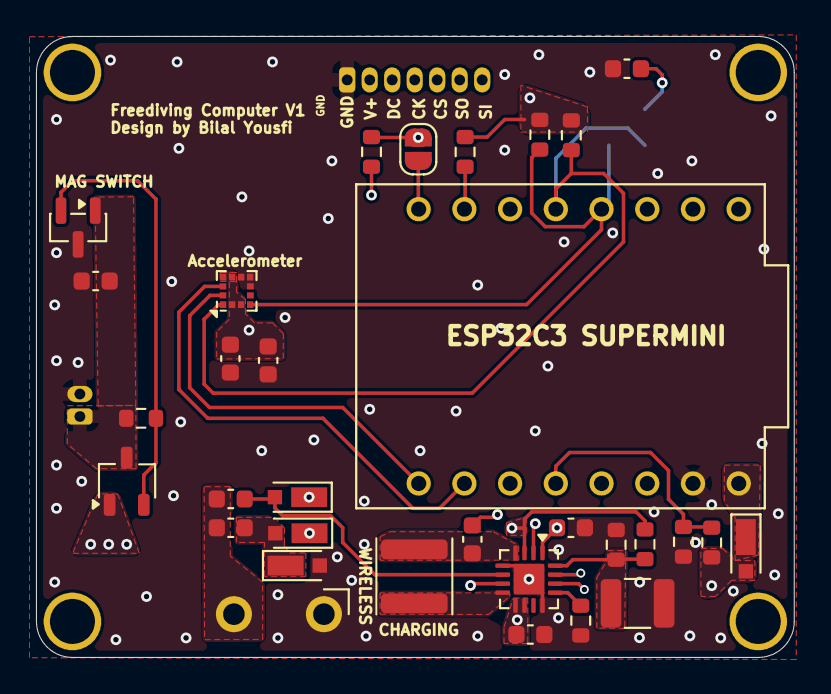
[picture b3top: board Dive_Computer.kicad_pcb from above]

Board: 4 copper layers, 42.1 x 34.5 mm, 35 parts (1 on the bottom side), 29 nets.

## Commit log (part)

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2026-04-27 Start
2026-04-27 Shematic
2026-04-28 Schematic finished
2026-04-29 Schematic update
2026-04-30 Routage terminé
2026-04-30 Added 3D models
2026-05-15 UI
    The UI is mostly done
    The core architecture is up and running
2026-05-15 added the software
2026-05-17 Readme update
2026-05-18 Revise README.md for improved presentation and details
    Updated README to enhance formatting and clarity, including new sections and features.
2026-05-18 Revise README.md for software architecture and UI
    Updated README.md to enhance software architecture and UI details, including FreeRTOS task management and tap-to-control navigation.
2026-06-08 Chargeur
2026-06-12 jaaj
